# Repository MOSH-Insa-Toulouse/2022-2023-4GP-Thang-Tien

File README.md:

# 2022-2023-4GP-Thang-Tien

# 1. Contexte et objectifs du projet
- [x] Réaliser une jauge de contrainte low-tech à base de graphite: [Pencil Drawn Strain Gauges and Chemiresistors on Paper](https://www.researchgate.net/publication/259846610_Pencil_Drawn_Strain_Gauges_and_Chemiresistors_on_Paper)
- [x] Concevoir un shield Arduino contenant l'amplificateur du capteur et les composants électroniques annexes (émetteur/récepteur Bluetooth, encodeur rotatif et écran OLED)
- [x] Réaliser une application mobile connectée à l'émetteur Bluetooth du capteur sous APP MIT INVENTOR 
- [x] Effectuer une évaluation du capteur sur un banc d'essai afin de produire une fiche technique et de comparer la technologie utilisée avec celle d'un autre capteur commercial similaire

# 2. Capteur de contrainte
> Notre capteur de contrainte utilise une jauge en papier équipée d'un circuit résistif en graphite, offrant l'avantage d'être facile à installer à moindre coût.
> La théorie de la percolation est exploitée dans ce capteur low-tech, qui est composé de nanoparticules de graphite formant des feuillets. Le réseau percolé caractéristique de la fine couche de graphite déposée sur la feuille de papier permet le transport des électrons entre les nanoparticules par l'effet tunnel. La déformation de la jauge en tension ou en compression entraîne une variation de la résistance de la couche de graphite, ce qui permet de mesurer la contrainte et la déformation appliquées.
> Le fonctionnement de notre jauge de contrainte repose sur la variation de la résistance du circuit résistif en fonction de sa déformation. Elle est alimentée par une tension régulée de 5V fournie par une carte Arduino UNO. Le courant circulant dans la jauge est mesuré pour fournir le signal du capteur, qui doit ensuite être amplifié et filtré.
  ## 2.1. Circuit amplificateur
  > La conductance des jauges en graphite que nous utilisons est très faible (de l'ordre de la dizaine de nS) et est alimentée par une tension continue de 5V. Le circuit amplificateur du capteur doit alors être en mesure d'extraire l'information d'un signal en courant de très faible intensité.
 > Dans ce projet, nous avons décidé d'utiliser un montage transimpédance constitué d'un amplificateur opérationnel (AOP) pour fournir un signal en tension suffisant au convertisseur analogique-numérique (ADC) d'une carte Arduino UNO.
 
 >   Notre jauge de contrainte est composée d'une seule résistance en série. De ce fait, notre signal est sensible aux dérives en tension de l'amplificateur. Notre AOP doit donc avoir un offset de tension en entrée très faible de manière à ce qu'il ne puisse fausser le signal fourni à l'ADC. Cela restreint notre choix d'amplificateur opérationnel. Nos jauges de contrainte en graphite ont une conductivité aux alentours de 10 nS. La jauge étant alimentée par 5V, nous nous attendons à avoir un signal en courant de l'ordre de 50 nA. En shuntant ce courant par une résistance de 100 kΩ, le signal en tension fourni à l'AOP est de 5 mV. À titre de comparaison, l'amplificateur [LM741](https://www.ti.com/lit/ds/symlink/lm741.pdf) présente un offset en entrée typique de 1 mV, et pouvant atteindre 5 mV. Ce composant n'est donc pas adapté pour notre utilisation. Ainsi notre amplificateur doit spécifiquement présenter un offset en entrée faible. Pour cette raison, nous utilisons le [LTC1050](https://www.analog.com/media/en/technical-documentation/data-sheets/1050fb.pdf), pour sa tension de dérive de 5 µV, soit 1000 fois plus faible que notre signal nominal de 5 mV.
 
 >   À partir de cet AOP, nous élaborons l'architecture du circuit amplificateur (cf. [Figure 1a](analog_circuit_images/analog_circuit.JPG)). Ce dernier dispose de trois étages de filtrage:
 >   - à l'entrée, un filtre passe-bas (R1C1) de fréquence de coupure de 16 Hz permet de filtrer les bruits en courant sur le signal d'entrée
 >   - un autre filtre passe bas de 1.6 Hz (R3C2) couplé à l'AOP permet de filtrer la composante du bruit à 50 Hz provenant du réseau électrique
 >   - à la sortie de l'amplificateur, un dernier filtre (R4C4) de 1.6 kHz permet de traiter les bruits dus à l'échantillonage de l'ADC

 >   La capacité C3 sert à filtrer les irrégularités de la tension d'alimentation de l'amplificateur. La résistance R2 sert à calibrer l'amplificateur sur le domaine de tension souhaité, qui est celui de l'ADC du micro-contrôleur. Lors de la phase de prototypage du circuit, nous avons utilisé un potentiomètre digital à la place de cette résistance pour trouver sa valeur. Enfin, la résistance R5 protège l'AOP contre les décharges électrostatiques et constitue un filtre RC avec la capacité C1 pour les bruits en tension.

 > <div class="row" align="center">
   > 
   > </div>
**Figure 1a - Circuit amplificateur transimpédance. La résistance *Rsensor* représente la jauge de contrainte.**
 
 > <div class="row" align="center">
   > 
   > </div>
**Figure 1b - Simulation AC du circuit amplificateur. Les fréquences de coupure à 1.6 Hz, 16 Hz et 1.6 kHz des trois filtres en cascade sont visibles. Cette simulation permet de vérifier le fonctionnement en fréquence de notre circuit.**

> Pour vérifier le fonctionnement normal du circuit sur LTSpice, nous simulons la déformation de la jauge par un pulse de tension en entrée (Figure 2). Ce pulse de tension génère une variation du courant en entrée de l'AOP. Virtuellement, cela représente la variation de conductance de la jauge due à sa déformation. Pour cette simulation, nous faisons varier la conductance de 5 nS à 20 nS, ce qui correspond à l'ordre de grandeur des jauges resistives utilisées. Ce faisant, nous balayons à peu près tout l'intervalle de signaux d'entrée possibles:

 > <div class="row" align="center">
   > 
   > </div>
**Figure 2 - Simulation du fonctionnement du circuit amplificateur. Un pulse de tension permet de modéliser la déformation de la jauge et la variation du signal en courant.**
 
 > <div class="row" align="center">
   > 
   > </div>
**Figure 3: Résultats de la simulation. En bleu, le signal en courant fourni par la jauge et en vert la tension de sortie de l'AOP.**

> En prenant en compte la plage de conductance considérée, le signal de sortie varie d'environ 240 mV à 1,05 V, ce qui ne sature pas l'ADC. L'amplitude crête-à-crête du bruit à 50 Hz est de 14 mV RMS. Ainsi, ce signal est détectable par l'ADC qui a une sensibilité d'environ 5 mV. Le rapport signal sur bruit est de 25,6 dB pour la conductance la plus faible et de 37,2 dB pour la conductance la plus élevée. Bien que notre signal dans cette simulation ne soit pas considéré comme optimal en termes d'instrumentation (rapport signal sur bruit inférieur à 40 dB), il est important de noter que plus le signal de sortie est élevé (c'est-à-dire plus la conductance est élevée), plus le bruit à 50 Hz est atténué par le signal. Cela signifie que des mesures plus fiables et précises peuvent être obtenues en utilisant des jauges de contrainte de résistance relativement faibles (environ 50 MΩ ou moins). Pour avoir une plus grande flexibilité quant aux conductances des jauges utilisées, il aurait été possible d'intégrer directement sur le PCB un potentiomètre numérique en remplacement de R2. Cela aurait permis, après une étape de calibration, d'adapter le signal de sortie à la jauge résistive utilisée afin d'obtenir un signal optimal. Cependant, si nous limitons l'utilisation de jauges présentant des conductances suffisamment élevées, nous obtenons un signal tout à fait acceptable.

  ## 2.2. Intégration Arduino
   > <div class="row" align="center">
   > 
   > </div>
  
   > <div class="row" align="center">
   > 
   > </div>

   > <div class="row" align="center">
   >  
   > </div>
  
   > <div class="row" align="center">
   >  
   > </div>
   
   > <div class="row" align="center">
   >  
   > </div>
  
   > <div class="row" align="center">
   >  
   > </div>
 
   **Figure 4 - Design du PCB.**

   > <div class="row" align="center">
   > 
   > </div>

   **Figure 5 - Circuit intergré des composants.** 

# 3. Programme Arduino
> Le programme Arduino permet de calculer la valeur de la résistance du capteur à partir de la valeur de tension mesurée par l'ADC de la carte. Cette mesure résistive est ensuite envoyée à l'application mobile via Bluetooth si cela est requis sur l'application. L'encodeur rotatif permet d'activer un menu sur l'OLED de choix d'affichage sur celui-ci : soit on affiche la valeur de la résistance, soit on affiche la valeur de la tension. On peut également choisir d'afficher une image ou les crédits (défilants).
> 
> A la mise en route du programme, une animation d'initialisation apparaît sur l'écran. Après cela, on a directement accès à la valeur résistive mesurée par le capteur. En tournant l'encodeur rotatoire, on peut rentrer dans le menu et sélectionner l'affichage de son choix toujours grâce à la rotation de l'encodeur. Ensuite, on valide le choix en faisant une pression sur l'encodeur.

# 4. Application mobile
> Dans le cadre de ce projet, nous avons programmé sur MIT APP INVENTOR, l'application mobile connectée au module Bluetooth du capteur. Cette dernière est constituée d'une seule activité sur laquelle il est possible d'acquérir les données du capteur en temps réel et de les tracer sur un graphique dynamique.
 > <div class="column" align="center">
 > 
 > </div>
 **Figure 6 - page d'accueil de la dernière version de l'application mobile. Cette capture d'écran a été prise pendant le fonctionnement du capteur.**
 
> On programme des blocks de fonction pour connecter Module Bluetooth HC05 et tracer le variation de resistance en temps.
 > <div class="column" align="center">
 > 
  **Figure 7 - Blocks Connection Bluetooth .**
 > 
 > 
 > 
   **Figure 7 - Blocks Initialiser programme et mapping valeur pour le graphe.**
 > 
 > 
  **Figure 7 - Blocks tracer le graphe.**
 > </div>

 > Pour la connection Bluetooth, le smartphone doit être appareillé au module du capteur avant de pouvoir se connecter via l'application mobile. L'application ne permet pas de choisir à quel module se connecter. En réalité, l'application est liée à un module bluetooth en particulier (celui fourni avec le capteur) et lui seul pourra être connecté au smartphone pour la transmission de données. Une piste d'amélioration consiste à afficher la liste des dispositifs appareillés pour se connecter au module souhaité. Nous n'avons cependant pas pu implémenter cette fonctionnalité par manque de temps.

 > N.B: le fichier .apk de l'application mobile est situé dans le répertoire suivant: [ici](https://github.com/MOSH-Insa-Toulouse/2022-2023-4GP-Thang-Tien/blob/0f889ce377105a8e069ff56407e032ddfc5c72b9/application%20Android/APP_PROJET_CAPTEUR.apk)
# 5. Mesures : Banc de test, datasheet et discussions
  ## 5.1. Banc de test
   > <div class="column" align="center">
 > 
 > </div>
  Nous utilisons ce banc de test composé de 7 demi cylindres de différents diamètres allant de 2 à 5 cm avec un pas de 0,5 cm. Nous posons le capteur sur chacun des cylindres et appliquons donc une déformation sur celui-ci. Cette déformation se retrouve avec la formule ci-dessous :
            $$\epsilon = \frac{e}{2r}$$
 La déformation ε dépend de l'épaisseur (**e**) de la feuille du capteur (nous avons prit pour ça 0.16mm qui est le grammage de feuille 140g/m²) et du rayon de courbure des cercles (**r**) donc le rayon de chaque demi cylindre. Nous avons réalisé les mesures en compression et en tension pour chacun de nos capteurs. 
  ## 5.2. Mesures et résultats
  
  On realise la test sur le capteur graphite de HB, 2H sous même tension entrée. 
  > <div class="column" align="center">
 > 
 > 
 > </div>
 
  Le pente de courbe de HB est inférieur à celui de 2H, correspondant au taux ΔR/R0 inférieur. Les mines les plus dures contiennent une grande quantité de liants argileux et donc moins de graphite, tandis que les mines plus tendres déposent une plus grande quantité de graphite sur le papier. Dans notre cas, cette différence de concentration de graphite sur le capteur influence sa résistance. C'est pourquoi les courbes associées aux mines HB présentent des valeurs de résistance (ΔR/R0) inférieures à celles de la mine 2H, qui est plus dure. 
  ## 5.3. Datasheet
  La fiche technique est disponible [ici](https://github.com/MOSH-Insa-Toulouse/2022-2023-4GP-Thang-Tien/blob/main/Datasheet/Datasheet_graphite_sensor.pdf).

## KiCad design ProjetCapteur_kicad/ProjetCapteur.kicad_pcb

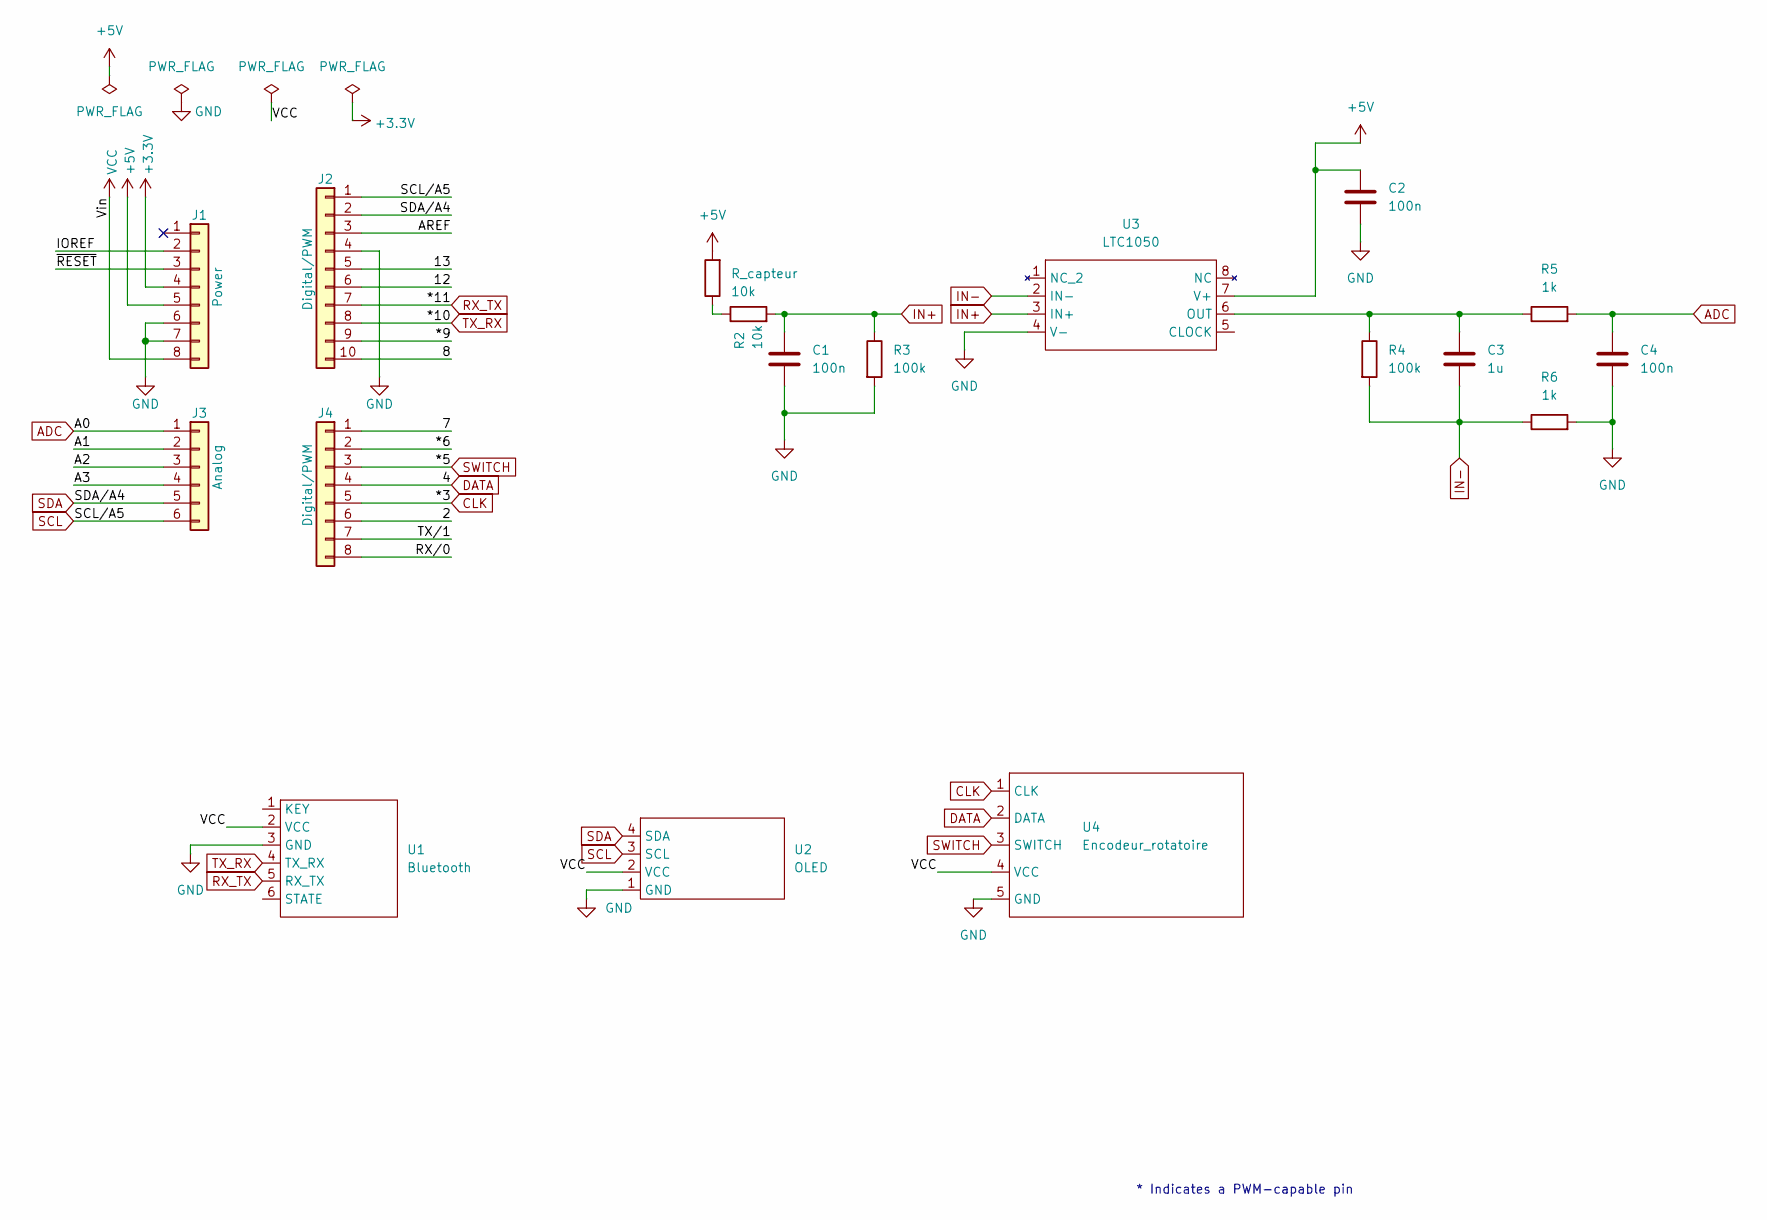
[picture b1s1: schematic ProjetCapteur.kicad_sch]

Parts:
C1, C2, C4: 100n; C_Disc_D5.0mm_W2.5mm_P5.00mm
C3: 1u; C_Rect_L9.0mm_W5.1mm_P7.50mm_MKT
J1: Power; PinSocket_1x08_P2.54mm_Vertical
J2: Digital/PWM; PinSocket_1x10_P2.54mm_Vertical
J3: Analog; PinSocket_1x06_P2.54mm_Vertical
J4: Digital/PWM; PinSocket_1x08_P2.54mm_Vertical
R2: 10k; R_Axial_DIN0207_L6.3mm_D2.5mm_P7.62mm_Horizontal
R3, R4: 100k; R_Axial_DIN0207_L6.3mm_D2.5mm_P7.62mm_Horizontal
R5, R6: 1k; R_Axial_DIN0207_L6.3mm_D2.5mm_P7.62mm_Horizontal
R_capteur: 10k; R_Axial_DIN0207_L6.3mm_D2.5mm_P7.62mm_Horizontal
U1: Bluetooth; BLUETOOTH_HC05
U2: OLED
U3: LTC1050
U4: Encodeur_rotatoire; KY_040

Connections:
+3V3: J1.4
+5V: C2.1, J1.5, R_capteur.2, U3.7 (V+); also elsewhere on the board
/2: J4.6
/7: J4.1
/8: J2.10
/12: J2.6
/13: J2.5
/*6: J4.2
/*9: J2.9
/A1: J3.2
/A2: J3.3
/A3: J3.4
/AREF: J2.3
/IOREF: J1.2
/RX/0: J4.8
/TX/1: J4.7
/~RESET: J1.3
ADC: C4.1, J3.1, R5.2
CLK: J4.5, U4.1 (CLK)
DATA: J4.4, U4.2 (DATA)
GND: C1.2, C2.2, C4.2, J1.6, J1.7, J2.4, R3.2, R6.2, U1.3 (GND), U2.1 (GND), U3.4 (V-), U4.5 (GND)
IN+: C1.1, R2.2, R3.1, U3.3 (IN+)
IN-: C3.2, R4.2, R6.1, U3.2 (IN-)
unnamed: C3.1, R4.1, R5.1, U3.6 (OUT)
unnamed 24: R2.1, R_capteur.1; also elsewhere on the board
RX_TX: J2.7, U1.5 (RX_TX)
SCL: J2.1, J3.6, U2.3 (SCL)
SDA: J2.2, J3.5, U2.4 (SDA)
SWITCH: J4.3, U4.3 (SWITCH)
TX_RX: J2.8, U1.4 (TX_RX)
VCC: J1.8, U1.2 (VCC), U2.2 (VCC), U4.4 (VCC)

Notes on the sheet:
* Indicates a PWM-capable pin

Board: 2 copper layers, 22 parts (0 on the bottom side), 15 nets, no tracks yet.

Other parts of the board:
MH1, MH2, MH3, MH4: MountingHole_3.2mm
R1: 10k; R_Axial_DIN0207_L6.3mm_D2.5mm_P7.62mm_Horizontal

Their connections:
+5V: R1.2; also elsewhere on the board
unnamed 24: R1.1; also elsewhere on the board
